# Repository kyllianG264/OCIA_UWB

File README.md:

# OCIA UWB

Depot organise pour une chaine UWB complete :

```text
Portenta UWB anchor -> UART Serial1 -> ESP8266 UDP broadcast -> Python receiver
Stella UWB tag      -> UWB responder
```

## Arduino

- `portenta/portenta.ino` : Portenta en anchor/controller. Il imprime `A1=<cm> D1=<cm> ...` en USB et sur `Serial1`.
- `portenta/UWBFeature.*` : feature UWB separee, reprise de ton decoupage.
- `portenta/PortentaWiFiUDP.*` : feature Wi-Fi/UDP optionnelle pour envoyer depuis la Portenta directement.
- `stella/stella.ino` : Stella en tag/responder.
- `esp/esp.ino` : bridge ESP8266. Il lit les lignes serie et les envoie en UDP broadcast sur le port `4210`.
- `libraries/README.md` : archives de librairies compatibles a installer dans Arduino IDE.

Pour plusieurs ancres, dupliquer le sketch Portenta et changer :

- `ANCHOR_ID`
- `SRC_ADDR`
- si besoin la session/adresse selon ton montage

Le Python sait lire `A1=123`, `A2=456`, etc.

## Python

Receiver simple :

```powershell
py python\udp_distance_viewer.py --port 4210 --anchor 1
```

Estimations :

```powershell
py -m pip install -r python\requirements.txt
py python\estimation_3d\main.py
py python\estimation_2d\main.py
py python\estimation_3d_to_2d\main.py
```

Mode UDP pour les estimateurs 2D :

```powershell
py python\estimation_2d\main.py --source udp --port 4210
py python\estimation_3d_to_2d\main.py --source udp --port 4210
```

## Cabling rapide

- Portenta `Serial1 TX` vers ESP8266 `RX`
- masses communes entre Portenta et ESP
- meme baudrate : `115200`
- PC et ESP sur le meme reseau Wi-Fi

L'ESP calcule l'adresse broadcast du reseau avec `WiFi.localIP()` et `WiFi.subnetMask()` puis envoie vers le port `4210`.

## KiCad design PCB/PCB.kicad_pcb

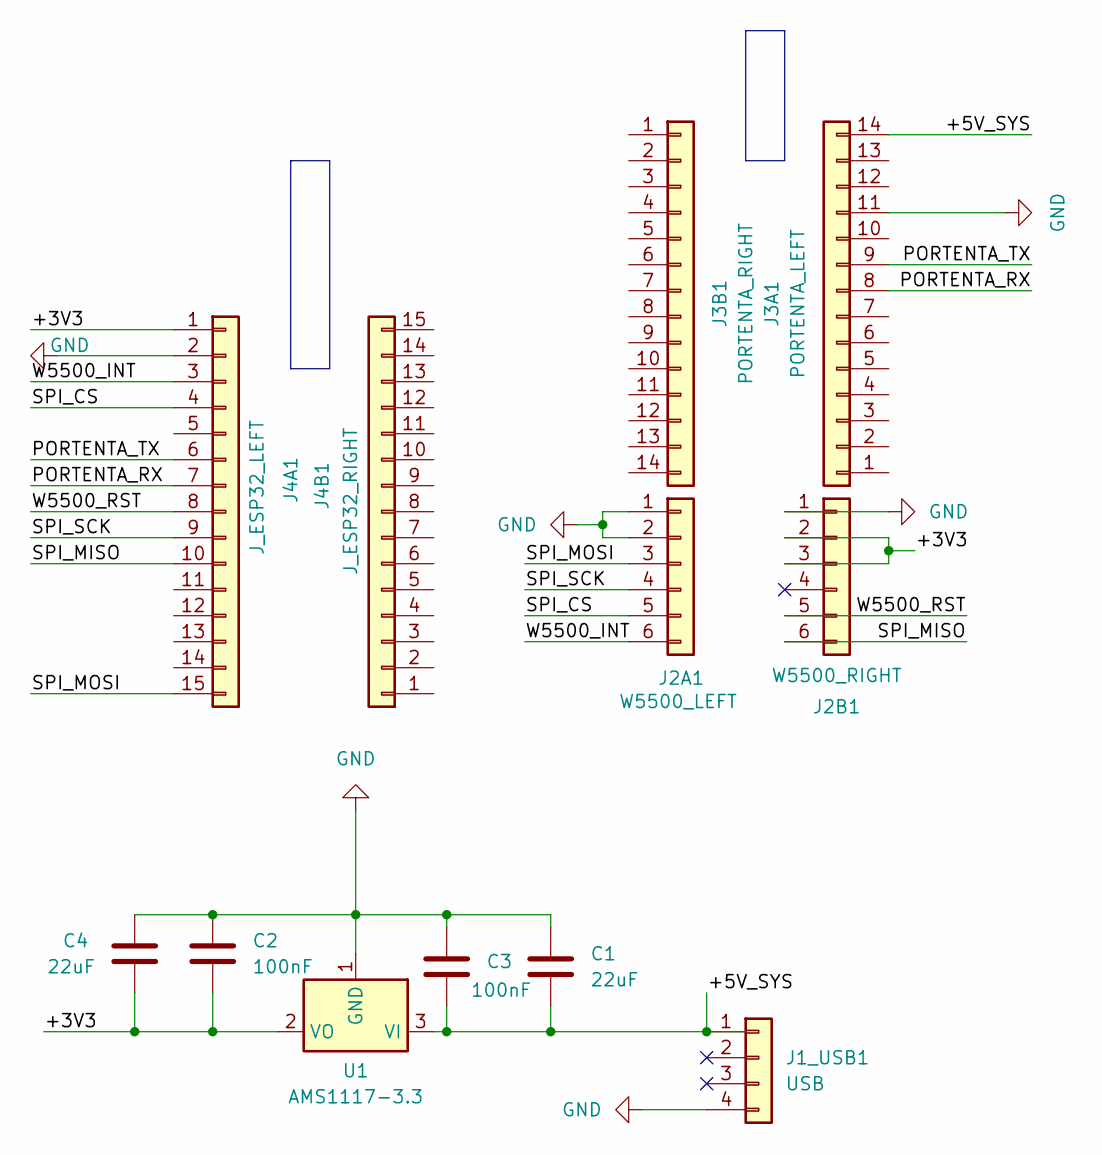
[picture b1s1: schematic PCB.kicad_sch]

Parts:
C1, C4: 22uF; C_1206_3216Metric
C2, C3: 100nF; C_0805_2012Metric
J1_USB1: USB; PinSocket_1x04_P2.54mm_Vertical
J2A1: W5500_LEFT; PinSocket_1x06_P2.54mm_Vertical
J2B1: W5500_RIGHT; PinSocket_1x06_P2.54mm_Vertical
J3A1: PORTENTA_LEFT; PinHeader_1x14_P2.54mm_Vertical
J3B1: PORTENTA_RIGHT; PinHeader_1x14_P2.54mm_Vertical
J4A1: J_ESP32_LEFT; PinSocket_1x15_P2.54mm_Vertical
J4B1: J_ESP32_RIGHT; PinSocket_1x15_P2.54mm_Vertical
U1: AMS1117-3.3; SOT-223-3_TabPin2

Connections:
/+3V3: C2.2, C4.2, J2B1.2, J2B1.3, J4A1.1, U1.2 (VO)
/+5V_SYS: C1.2, C3.2, J1_USB1.1, J3A1.14, U1.3 (VI)
/PORTENTA_RX: J3A1.8, J4A1.7
/PORTENTA_TX: J3A1.9, J4A1.6
/SPI_CS: J2A1.5, J4A1.4
/SPI_MISO: J2B1.6, J4A1.10
/SPI_MOSI: J2A1.3, J4A1.15
/SPI_SCK: J2A1.4, J4A1.9
/W5500_INT: J2A1.6, J4A1.3
/W5500_RST: J2B1.5, J4A1.8
GND: C1.1, C2.1, C3.1, C4.1, J1_USB1.4, J2A1.1, J2A1.2, J2B1.1, J3A1.11, J4A1.2, U1.1 (GND)

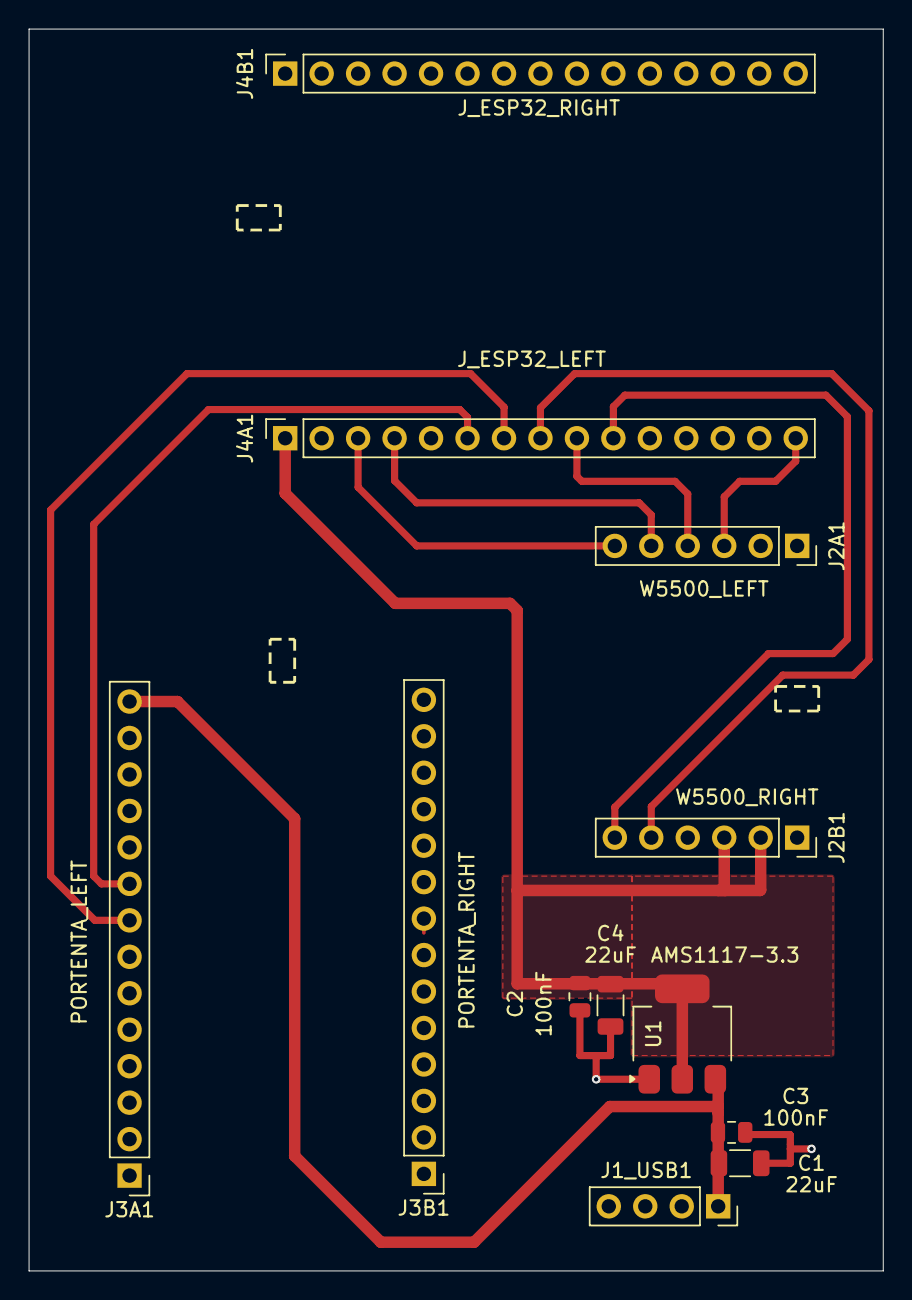
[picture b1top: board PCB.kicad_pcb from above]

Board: 2 copper layers, 59.5 x 86.5 mm, 12 parts (0 on the bottom side), 11 nets.

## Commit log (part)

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2026-02-11 V1 Stella et Portenta First setup + Distance 1D
2026-02-11 V2 Callback Portenta
2026-02-11 V1 Portenta main 2 distances + Stella 2 anchor
2026-02-11 V3 OK
2026-03-12 V4 Pred python
2026-03-16 V1 2D 2D->3D 3D Simulation
2026-05-04 V4 PCB
2026-05-08 Revert "Merge branch 'main' of https://github.com/kyllianG264/OCIA_UWB"
    This reverts commit 6c5da00ebd873bafbee178729e910204b652e3fb, reversing
    changes made to 2a71bb6e980951c033e969d9675ea213bf3dacf8.
2026-05-08 V5 PCB A Goeury
2026-05-12 V7 python
2026-05-12 V8 Add ESP docs and PCB updates, adjust KiCad layout
    Add ESP documentation (images + PDF) and an ESP32_PIN_MAPPING guide; include PCB fabrication PDFs and multiple PCB backups. Update KiCad project files (.kicad_pcb, .kicad_pro, .kicad_sch): reposition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
2026-05-13 V9 python Meme logiciel et simulation Basket
2026-06-04 Add NeptuVisionS2 project and pipeline
    Initial import of the NeptuVisionS2 project. Adds project scaffold and .gitignore, a CLI orchestrator (app/pipeline.py) to run detection → projection → tracking → render → solver steps, core utilitie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
2026-06-22 V7 Solver
